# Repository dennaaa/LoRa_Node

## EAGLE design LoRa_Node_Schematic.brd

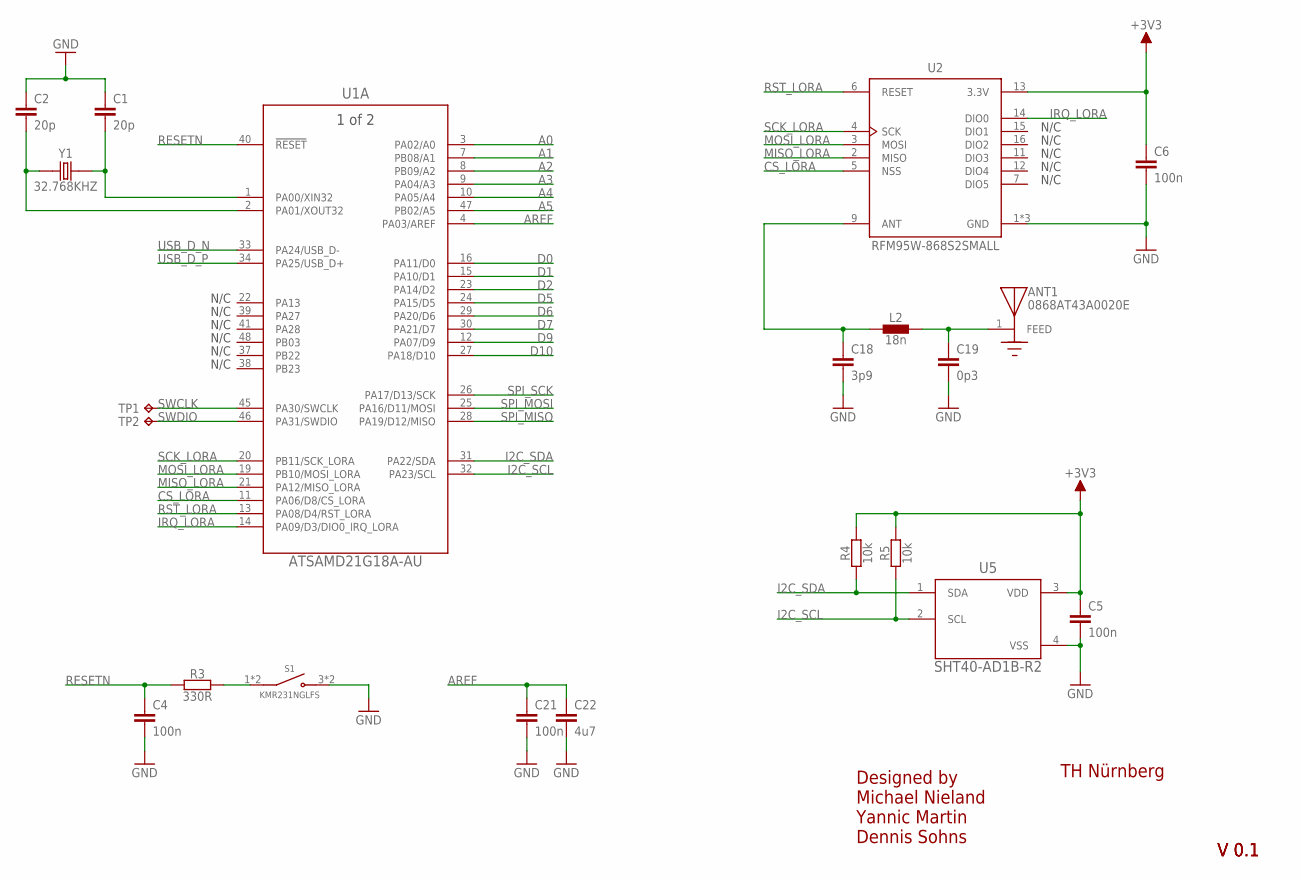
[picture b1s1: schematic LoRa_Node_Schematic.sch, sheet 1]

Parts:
ANT1: 0868AT43A0020E; XCVR_0868AT43A0020E
C1, C2: 20p; C0402
C4, C5, C6, C21: 100n; C0402
C18: 3p9; C0402; MANUFACTURE_PN 500R07S3R9BV4T
C19: 0p3; C0402; MANUFACTURER_PN 500R07S0R3BV4T
C22: 4u7; C0603
L2: 18n; R0402; MANUFACTURER_PN L-07C18NJV6T
R3: 330R; R0402
R4, R5: 10k; R0402
S1: KMR231NGLFS; SW_KMR231NGLFS
TP1, TP2: TPTP10R; TP10R
U1: ATSAMD21G18A-AU; TQFP48_7X7MC_MCH
U2: RFM95W-868S2SMALL; MICROBUILDER_RFMHCW_SMT
U5: SHT40-AD1B-R2; SHT4X_SEN
Y1: 32.768KHZ; XTAL_ABS07-32.768KHZ-T

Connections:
+3V3: C5.1, C6.1, R4.2, R5.2, U2.13 (3.3V), U5.3 (VDD); also elsewhere on the board
A0: U1.3 (PA02/A0); also elsewhere on the board
A1: U1.7 (PB08/A1); also elsewhere on the board
A2: U1.8 (PB09/A2); also elsewhere on the board
A3: U1.9 (PA04/A3); also elsewhere on the board
A4: U1.10 (PA05/A4); also elsewhere on the board
A5: U1.47 (PB02/A5); also elsewhere on the board
ANTENNA: C18.1, L2.1, U2.9 (ANT)
ANTENNA_L: ANT1.1, C19.1, L2.2
AREF: C21.1, C22.1, U1.4 (PA03/AREF); also elsewhere on the board
CS_LORA: U1.11 (PA06/D8/CS_LORA), U2.5 (NSS)
D0: U1.16 (PA11/D0); also elsewhere on the board
D1: U1.15 (PA10/D1); also elsewhere on the board
D2: U1.23 (PA14/D2); also elsewhere on the board
D5: U1.24 (PA15/D5); also elsewhere on the board
D6: U1.29 (PA20/D6); also elsewhere on the board
D7: U1.30 (PA21/D7); also elsewhere on the board
D9: U1.12 (PA07/D9); also elsewhere on the board
D10: U1.27 (PA18/D10); also elsewhere on the board
GND: C1.1, C2.1, C4.2, C5.2, C6.2, C18.2, C19.2, C21.2, C22.2, S1.3 (NO), S1.4 (NO), U2.1 (GND), U2.8 (GND), U2.10 (GND), U5.4 (VSS); also elsewhere on the board
I2C_SCL: R5.1, U1.32 (PA23/SCL), U5.2 (SCL); also elsewhere on the board
I2C_SDA: R4.1, U1.31 (PA22/SDA), U5.1 (SDA); also elsewhere on the board
IRQ_LORA: U1.14 (PA09/D3/DIO0_IRQ_LORA), U2.14 (DIO0)
MISO_LORA: U1.21 (PA12/MISO_LORA), U2.2 (MISO)
MOSI_LORA: U1.19 (PB10/MOSI_LORA), U2.3 (MOSI)
RESETN: C4.1, R3.1, U1.40 (!RESET)
RESETN_R: R3.2, S1.1 (COM), S1.2 (COM)
RST_LORA: U1.13 (PA08/D4/RST_LORA), U2.6 (RESET)
SCK_LORA: U1.20 (PB11/SCK_LORA), U2.4 (SCK)
SPI_MISO: U1.28 (PA19/D12/MISO); also elsewhere on the board
SPI_MOSI: U1.25 (PA16/D11/MOSI); also elsewhere on the board
SPI_SCK: U1.26 (PA17/D13/SCK); also elsewhere on the board
SWCLK: TP1.TP, U1.45 (PA30/SWCLK)
SWDIO: TP2.TP, U1.46 (PA31/SWDIO)
USB_D_N: U1.33 (PA24/USB_D-); also elsewhere on the board
USB_D_P: U1.34 (PA25/USB_D+); also elsewhere on the board
XIN32: C1.2, U1.1 (PA00/XIN32), Y1.2
XOUT32: C2.2, U1.2 (PA01/XOUT32), Y1.1

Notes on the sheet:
V 0.1
TH Nürnberg
Designed by Michael Nieland Yannic Martin Dennis Sohns
N/C

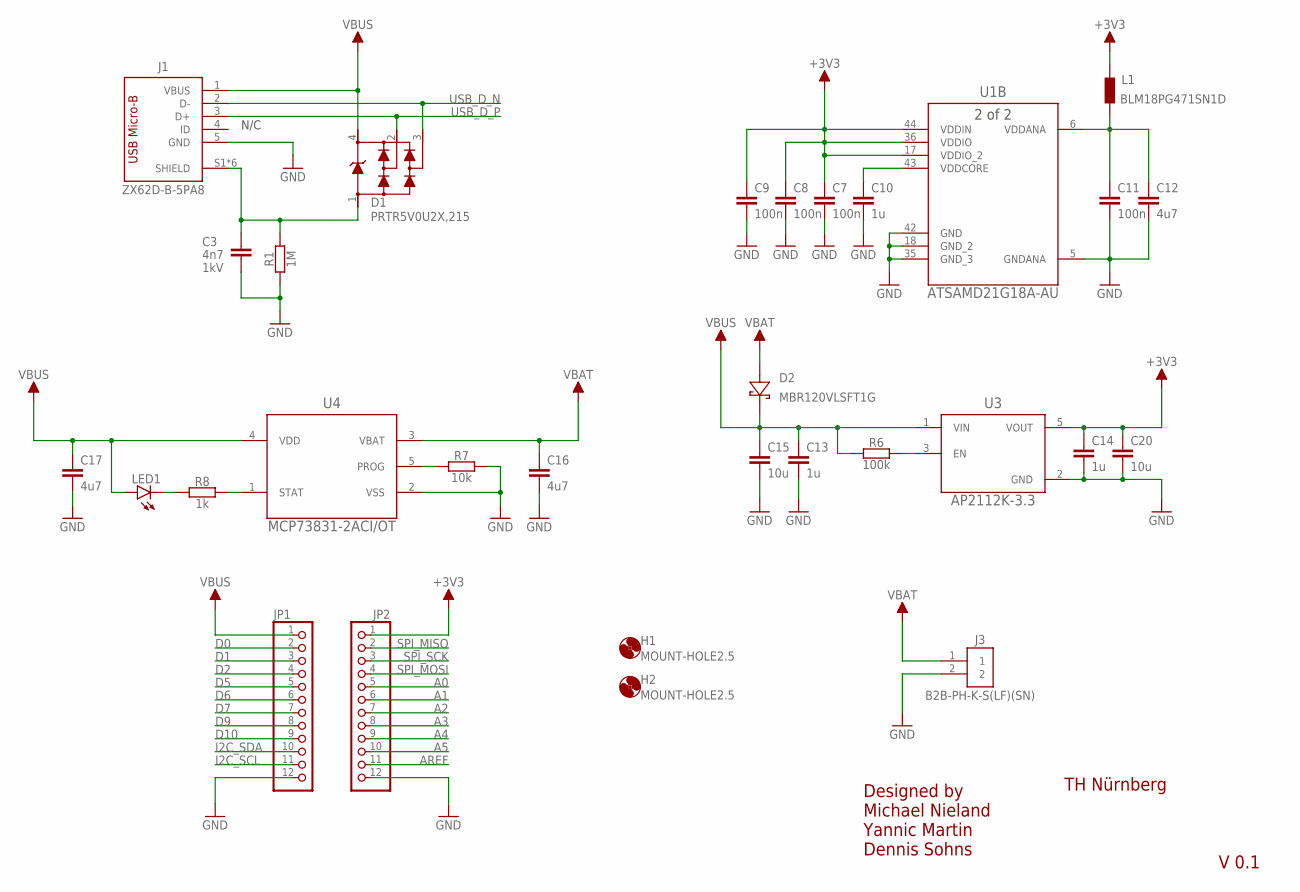
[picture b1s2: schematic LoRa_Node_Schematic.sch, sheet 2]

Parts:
C3: 4n7; C0805; VOLTAGE 1kV
C7, C8, C9, C11: 100n; C0402
C10, C13, C14: 1u; C0402
C12, C16, C17: 4u7; C0603
C15, C20: 10u; C0603
D1: PRTR5V0U2X,215; SOT143B
D2: MBR120VLSFT1G; SDO_SOD-123FL_ONS
H1, H2: MOUNT-HOLE2.5; MICROBUILDER_MOUNTINGHOLE_2.5_PLATED
J1: ZX62D-B-5PA8; HIROSE_ZX62D-B-5PA8
J3: B2B-PH-K-S(LF)(SN); JST_B2B-PH-K-S(LF)(SN)
JP1, JP2: PINHD-1X12-CB; 1X12-CB
L1: BLM18PG471SN1D; IND_BLM18_0603_MUR
LED1: LEDCHIP-LED0805; CHIP-LED0805
R1: 1M; R0402
R6: 100k; R0402
R7: 10k; R0402
R8: 1k; R0402
U1: ATSAMD21G18A-AU; TQFP48_7X7MC_MCH
U3: AP2112K-3.3; SOT95P285X140-5N
U4: MCP73831-2ACI/OT; SOT95P280X145-5N

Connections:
3V3_EN: R6.2, U3.3 (EN)
+3V3: C7.1, C8.1, C9.1, C14.1, C20.1, JP2.1, L1.1, U1.17 (VDDIO_2), U1.36 (VDDIO), U1.44 (VDDIN), U3.5 (VOUT); also elsewhere on the board
A0: JP2.5; also elsewhere on the board
A1: JP2.6; also elsewhere on the board
A2: JP2.7; also elsewhere on the board
A3: JP2.8; also elsewhere on the board
A4: JP2.9; also elsewhere on the board
A5: JP2.10; also elsewhere on the board
AREF: JP2.11; also elsewhere on the board
D0: JP1.2; also elsewhere on the board
D1: JP1.3; also elsewhere on the board
D2: JP1.4; also elsewhere on the board
D5: JP1.5; also elsewhere on the board
D6: JP1.6; also elsewhere on the board
D7: JP1.7; also elsewhere on the board
D9: JP1.8; also elsewhere on the board
D10: JP1.9; also elsewhere on the board
GND: C3.2, C7.2, C8.2, C9.2, C10.2, C11.2, C12.2, C13.2, C14.2, C15.2, C16.2, C17.2, C20.2, J1.5 (GND), J3.2, JP1.12, JP2.12, R1.1, R7.2, U1.5 (GNDANA), U1.18 (GND_2), U1.35 (GND_3), U1.42 (GND), U3.2 (GND), U4.2 (VSS); also elsewhere on the board
I2C_SCL: JP1.11; also elsewhere on the board
I2C_SDA: JP1.10; also elsewhere on the board
SPI_MISO: JP2.2; also elsewhere on the board
SPI_MOSI: JP2.4; also elsewhere on the board
SPI_SCK: JP2.3; also elsewhere on the board
USB_D_N: D1.3, J1.2 (D-); also elsewhere on the board
USB_D_P: D1.2, J1.3 (D+); also elsewhere on the board
USB_SHIELD: C3.1, D1.1, J1.S1 (SHIELD), J1.S2 (SHIELD), J1.S3 (SHIELD), J1.S4 (SHIELD), J1.S5 (SHIELD), J1.S6 (SHIELD), R1.2
VBAT: C16.1, D2.2 (12), J3.1, U4.3 (VBAT)
VBAT_PROG: R7.1, U4.5 (PROG)
VBAT_STAT: R8.2, U4.1 (STAT)
VBAT_STAT_R: LED1.C, R8.1
VBUS: C13.1, C15.1, C17.1, D1.4, D2.1 (11), J1.1 (VBUS), JP1.1, LED1.A, R6.1, U3.1 (VIN), U4.4 (VDD)
VDDANA: C11.1, C12.1, L1.2, U1.6 (VDDANA)
VDDCORE: C10.1, U1.43 (VDDCORE)

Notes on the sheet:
V 0.1
TH Nürnberg
Designed by Michael Nieland Yannic Martin Dennis Sohns
N/C

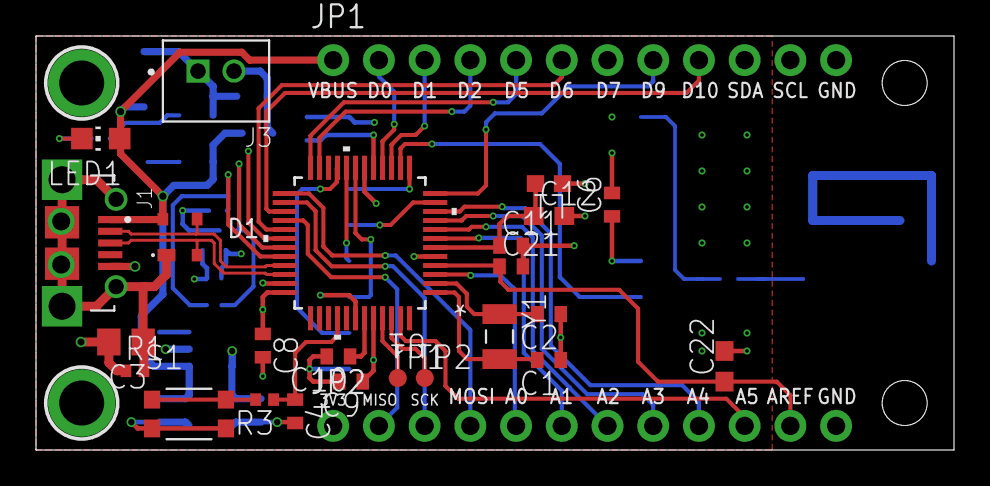
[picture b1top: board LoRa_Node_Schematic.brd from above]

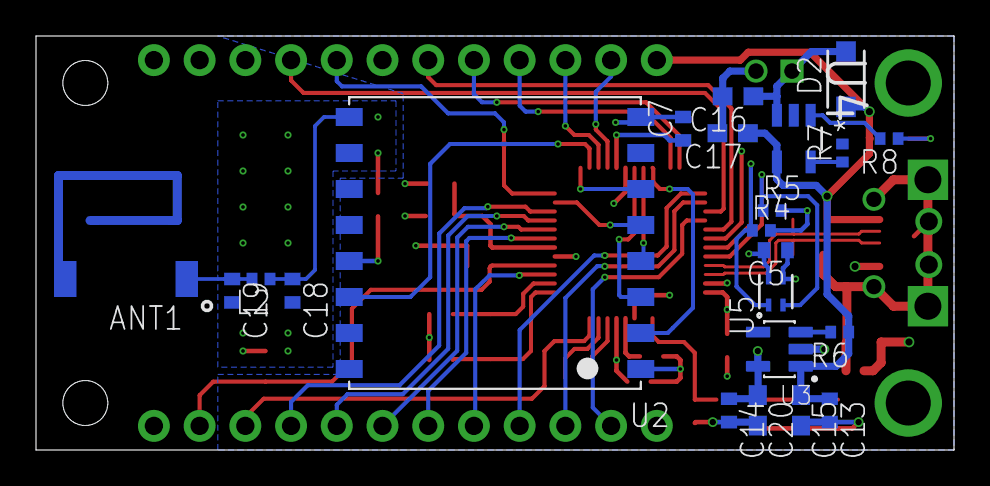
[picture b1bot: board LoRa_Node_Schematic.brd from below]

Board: 4 copper layers, 51.0 x 23.0 mm, 50 parts (22 on the bottom side), 47 nets.

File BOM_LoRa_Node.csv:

;Qty;Value;Device;Package;Parts;Description;AVAILABILITY;BUILT_BY;COPYRIGHT;DATASHEET;DESCRIPTION;DIGI-KEY_PART_NUMBER;MANUFACTURER;MANUFACTURER-PN;MANUFACTURER_PART_NUMBER;MANUFACTURER_PN;MANUFACTURE_PN;MF;MP;PACKAGE;POPULARITY;PRICE;PURCHASE-URL;SOURCELIBRARY;SPICEPREFIX;TP_SIGNAL_NAME;VENDOR;VOLTAGE
Open;1;;LEDCHIP-LED0805;CHIP-LED0805;LED1;LED;;;;;;;;;;;;;;;68;;;;;;;
Open;2;;PINHD-1X12-CB;1X12-CB;JP1, JP2;PIN HEADER;;;;;;;;;;;;;;;;;;;;;;
Farnell;1;0868AT43A0020E;0868AT43A0020E;XCVR_0868AT43A0020E;ANT1;Antenna 868mhz For Ti Cc11xx;;;;; 868MHz Chip RF Antenna 858MHz ~ 878MHz -1dBi Solder Surface Mount ;712-1399-1-ND;;;;;;Johanson Technology;0868AT43A0020E;None;;;https://pricing.snapeda.com/search/part/0868AT43A0020E/?ref=eda;;;;;
Mouser;1;0p3;C-EUC0402;C0402;C19;CAPACITOR, European symbol;;;;;;;Johanson Technology;;;500R07S0R3BV4T;;;;;18;;;;C;;;
Open;1;100k;R-EU_R0402;R0402;R6;RESISTOR, European symbol;;;;;;;;;;;;;;;0;;;;R;;;
Open;8;100n;C-EUC0402;C0402;C4, C5, C6, C7, C8, C9, C11, C21;CAPACITOR, European symbol;;;;;;;;;;;;;;;18;;;;C;;;
Open;3;10k;R-EU_R0402;R0402;R4, R5, R7;RESISTOR, European symbol;;;;;;;;;;;;;;;0;;;;R;;;
Open;2;10u;C-EUC0603;C0603;C15, C20;CAPACITOR, European symbol;;;;;;;;;;;;;;;73;;;;C;;;
Mouser;1;18n;INDUCTOR_0402_SMD;R0402;L2;;;;;;;;Johanson Technology;;;L-07C18NJV6T;;;;;;;;;;;;
Open;1;1M;R-EU_R0402;R0402;R1;RESISTOR, European symbol;;;;;;;;;;;;;;;0;;;;R;;;
Open;1;1k;R-EU_R0402;R0402;R8;RESISTOR, European symbol;;;;;;;;;;;;;;;0;;;;R;;;
Open;3;1u;C-EUC0402;C0402;C10, C13, C14;CAPACITOR, European symbol;;;;;;;;;;;;;;;18;;;;C;;;
Open;2;20p;C-EUC0402;C0402;C1, C2;CAPACITOR, European symbol;;;;;;;;;;;;;;;18;;;;C;;;
Farnell;1;32.768KHZ;ABS07-32.768KHZ-T;XTAL_ABS07-32.768KHZ-T;Y1;ABS07 Series 32.768 kHz ±20 ppm 12.5 pF -40 to +85 °C SMT Low Profile Crystal;;;;; 32.768kHz ±20ppm Crystal 12.5pF 70 kOhms 2-SMD, No Lead ;535-9542-1-ND;;;;;;Abracon;ABS07-32.768KHZ-T;SMD-2 Abracon LLC;;;https://pricing.snapeda.com/search/part/ABS07-32.768KHZ-T/?ref=eda;;;;;
Open;1;330R;R-EU_R0402;R0402;R3;RESISTOR, European symbol;;;;;;;;;;;;;;;0;;;;R;;;
Open;1;3p9;C-EUC0402;C0402;C18;CAPACITOR, European symbol;;;;;;;Johanson Technology;;;;500R07S3R9BV4T;;;;18;;;;C;;;
Farnell;1;4n7;C-EUC0805;C0805;C3;CAPACITOR, European symbol;;;;;;;KEMET;C0805C472KDRACTU;;;;;;;88;;;;C;;;1kV
Open;4;4u7;C-EUC0603;C0603;C12, C16, C17, C22;CAPACITOR, European symbol;;;;;;;;;;;;;;;73;;;;C;;;
Mouser;1;AP2112K-3.3;AP2112K-3.3;SOT95P285X140-5N;U3;AP2112 Series 0.6 A 3.3 V Fixed Output SMT LDO Linear Regulator - SOT23-5 Check prices;Good;;;; Linear Voltage Regulator IC 1 Output 600mA SOT-25 ;;;;;;;Diodes Inc.;AP2112K-3.3;SOT-753 Diodes Inc.;;None;https://pricing.snapeda.com/search/part/AP2112K-3.3TRG1/?ref=eda;;;;;
Mouser;1;ATSAMD21G18A-AU;ATSAMD21G18A-AU;TQFP48_7X7MC_MCH;U1;;;EMA_Molly;Copyright (C) 2018 Accelerated Designs. All rights reserved;;;;;;ATSAMD21G18A-AU;;;;;;;;;Microchip_2019-08-23_25;;;Microchip;
Farnell;1;B2B-PH-K-S(LF)(SN);B2B-PH-K-S(LF)(SN);JST_B2B-PH-K-S(LF)(SN);J3;PH Series 2 Position 2 mm Pitch Through Hole Top Entry Shrouded Header Check prices;Good;;;; Connector Header Through Hole 2 position 0.079 (2.00mm) ;;;;;;;JST Sales;B2B-PH-K-S(LF)(SN);None;;None;https://pricing.snapeda.com/search/part/B2B-PH-K-S(LF)(SN)/?ref=eda;;;;;
Mouser;1;BLM18PG471SN1D;BLM18PG471SN1D;IND_BLM18_0603_MUR;L1;;;EMA_UL_Team;;;;;;;BLM18PG471SN1D;;;;;;;;;Murata_2010-01-01IND_BLM;;;MURATA;
Mouser;1;KMR231NGLFS;KMR231NGLFS;SW_KMR231NGLFS;S1;Tactile Switch SPST-NO Top Actuated Surface Mount  Check prices;Good;;;; Tactile Switch SPST-NO Top Actuated Surface Mount ;;;;;;;C&K Components;KMR231NGLFS;None;;None;https://pricing.snapeda.com/search/part/KMR211NGLFS/?ref=eda;;;;;
Mouser;1;MBR120VLSFT1G;MBR120VLSFT1G;SDO_SOD-123FL_ONS;D2;;;EMA_Cory;Copyright (C) 2018 Accelerated Designs. All rights reserved;https://www.onsemi.com/pub/Collateral/MBR120VLSFT1-D.PDF;;;;;MBR120VLSFT1G;;;;;;;;;ON_Semiconductor_2020-09-15;;;ON Semiconductor;
Mouser;1;MCP73831-2ACI/OT;MCP73831-2ACI/OT;SOT95P280X145-5N;U4;Charge Management Controller Check prices;Good;;;; Charger IC Lithium Ion/Polymer SOT-23-5 ;;;;;;;Microchip;MCP73831-2ACI/OT;SOT-23 Microchip;;None;https://pricing.snapeda.com/search/part/MCP73831T-2ACI/OT/?ref=eda;;;;;
;2;MOUNT-HOLE2.5;MOUNT-HOLE2.5;MICROBUILDER_MOUNTINGHOLE_2.5_PLATED;H1, H2;;;;;;;;;;;;;;;;;;;;;;;
Mouser;1;PRTR5V0U2X,215;PRTR5V0U2X,215;SOT143B;D1;Ultra low capacitance double rail-to-rail ESD protection diode Check prices;Good;;;; Clamp Ipp Tvs Diode Surface Mount SOT-143B ;;;;;;;Nexperia USA Inc.;PRTR5V0U2X,215;TO-253-4 Nexperia USA Inc.;;None;https://pricing.snapeda.com/search/part/PRTR5V0U2X,215/?ref=eda;;;;;
Antratek;1;RFM95W-868S2SMALL;RFM95W-868S2SMALL;MICROBUILDER_RFMHCW_SMT;U2;RFM95(W) - Low Power Long Range Transceiver Module V1.0 Check prices;;;;;;;;;;;;;;;;;;;;;;
Mouser;1;SHT40-AD1B-R2;SHT40-AD1B-R2;SHT4X_SEN;U5;;;EMA_Cory;Copyright (C) 2018 Accelerated Designs. All rights reserved;https://www.mouser.com/datasheet/2/682/Sensirion_10272020_Da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;;;;;SHT40-AD1B-R2;;;;;;;;;Add_to_database_2020-11-16;;;Sensirion;
;2;TPTP10R;TPTP10R;TP10R;TP1, TP2;Test pad;;;;;;;;;;;;;;;3;;;;;;;
Mouser;1;ZX62D-B-5PA8;ZX62D-B-5PA8;HIROSE_ZX62D-B-5PA8;J1;CONN RCPT USB Check prices;Bad;;;; USB - micro B USB 2.0 Receptacle Connector 5 Position Surface Mount, Right Angle; Through Hole ;;;;;;;Hirose;ZX62D-B-5PA8;None;;None;;;;;

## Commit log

2020-12-18 done
2020-12-21 update 201221
2020-12-29 update29.12
2020-12-30 Review Version
2021-01-11 layout_finish
2021-01-13 uodate

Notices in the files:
BOM_LoRa_Node.csv:
1;SHT40-AD1B-R2;SHT40-AD1B-R2;SHT4X_SEN;U5;;;EMA_Cory;Copyright (C) 2018 Accelerated Designs. All rights reserved;https://www.mouser.com/datasheet/2/682/Sensirion_10272020_Datasheet_SHT4x-1919523.pdf;;;;;SHT40-AD1B-R2;;;;;;;;;Add_to_database_2020-11-16;;;Sensirion;
parts and their libraries:
COPYRIGHT: Copyright (C) 2018 Accelerated Designs. All rights reserved
